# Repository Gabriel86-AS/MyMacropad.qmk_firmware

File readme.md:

PROJECT: A macropad for symbols i use constantly but I often have to copy past them or search for their code to type it in the numerical keyboard.
 (Em Dash)
(Caret)
(Square Root)
(Ohm)
(Plus-Minus)
(Pi)
(Approximately Equal)

To use it should be pretty simple, just solder the components and plug it to the computer (in theory) should work.

I made this project to start learning hardware design

PICTURES

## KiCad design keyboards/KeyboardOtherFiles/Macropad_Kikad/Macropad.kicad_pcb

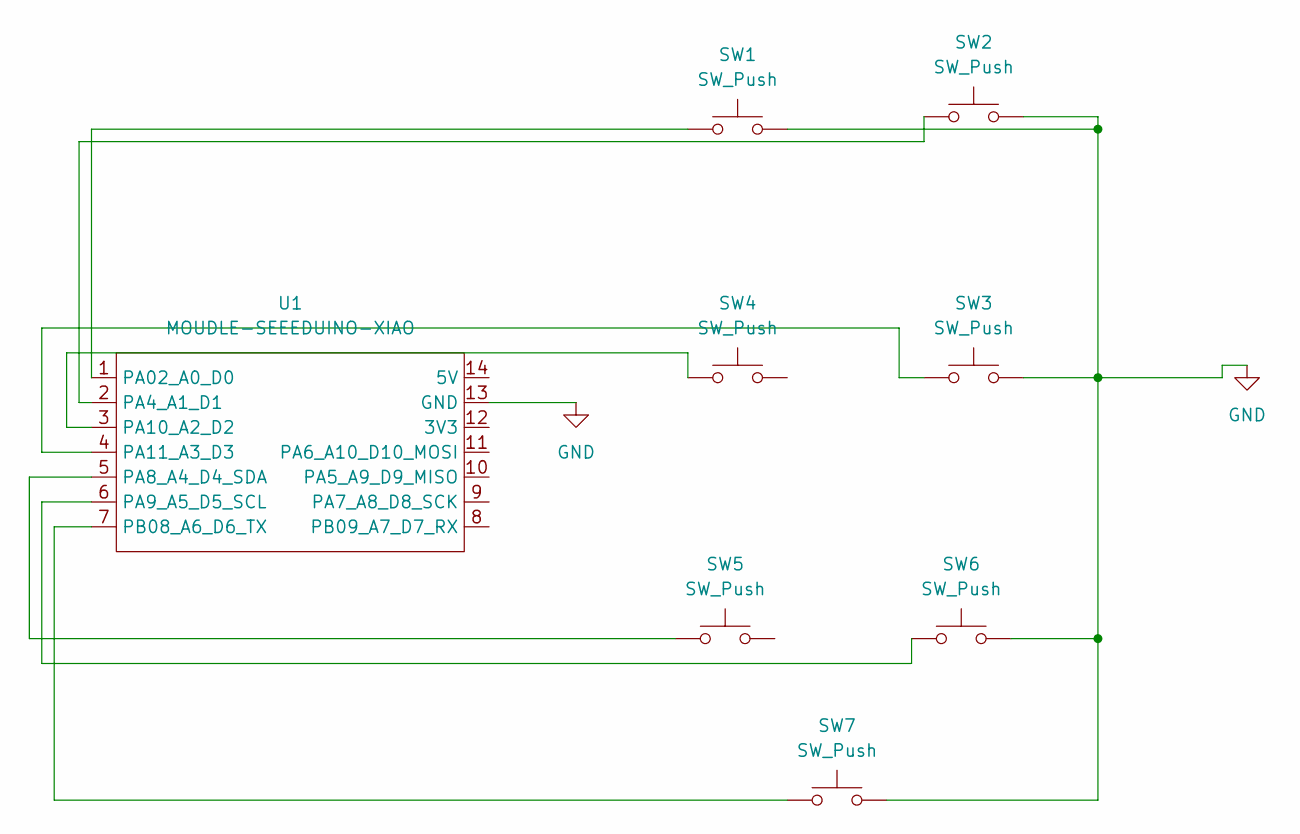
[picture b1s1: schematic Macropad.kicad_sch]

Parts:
SW1, SW2, SW3, SW4, SW5, SW6, SW7: SW_Push; SW_Cherry_MX_1.00u_PCB
U1: MOUDLE-SEEEDUINO-XIAO; XIAO-Generic-Hybrid-14P-2.54-21X17.8MM

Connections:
GND: SW1.2, SW2.2, SW3.2, SW6.2, SW7.2, U1.13 (GND)
unnamed: SW1.1, U1.1 (PA02_A0_D0)
unnamed: SW2.1, U1.2 (PA4_A1_D1)
unnamed: SW5.1, U1.5 (PA8_A4_D4_SDA)
unnamed: SW6.1, U1.6 (PA9_A5_D5_SCL)
unnamed: SW4.1, U1.3 (PA10_A2_D2)
unnamed: SW3.1, U1.4 (PA11_A3_D3)
unnamed: SW7.1, U1.7 (PB08_A6_D6_TX)

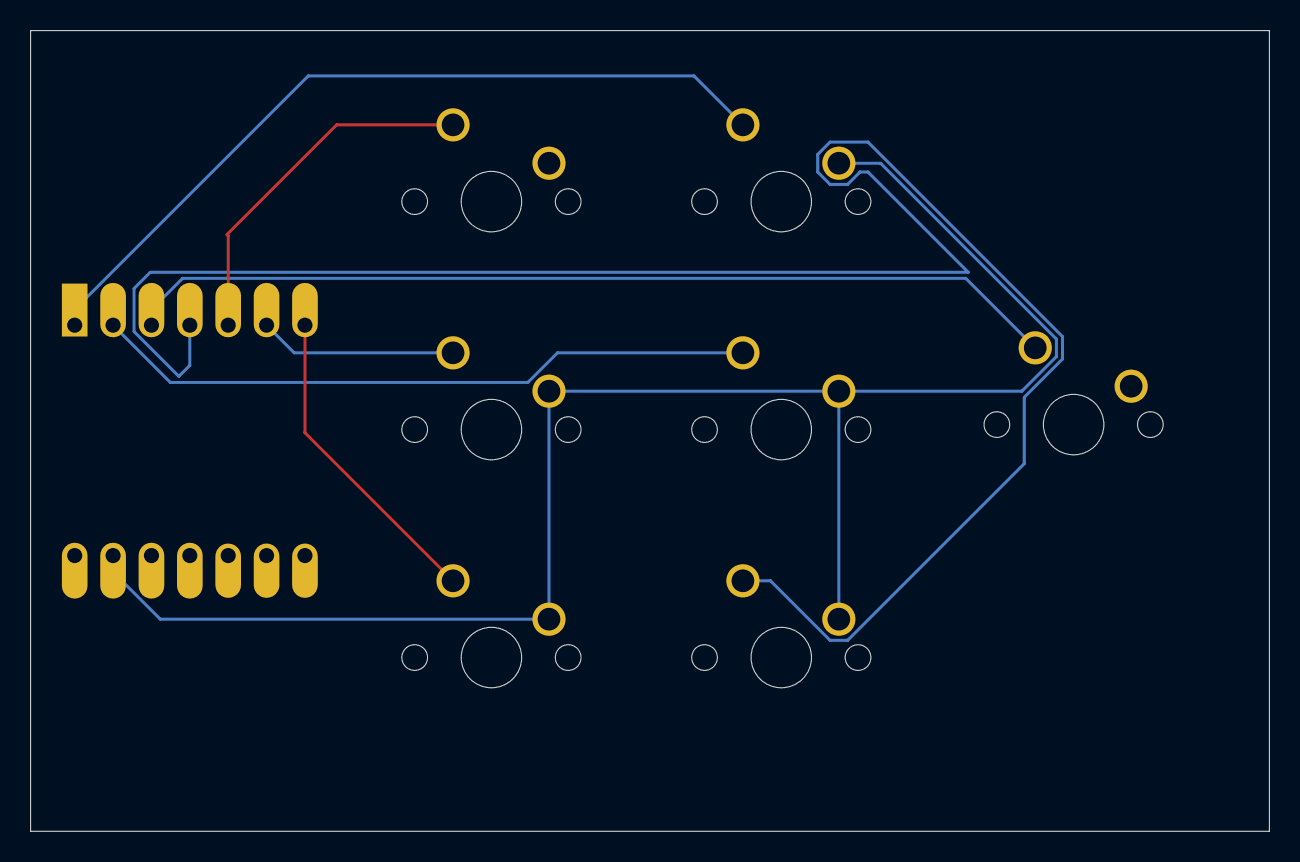
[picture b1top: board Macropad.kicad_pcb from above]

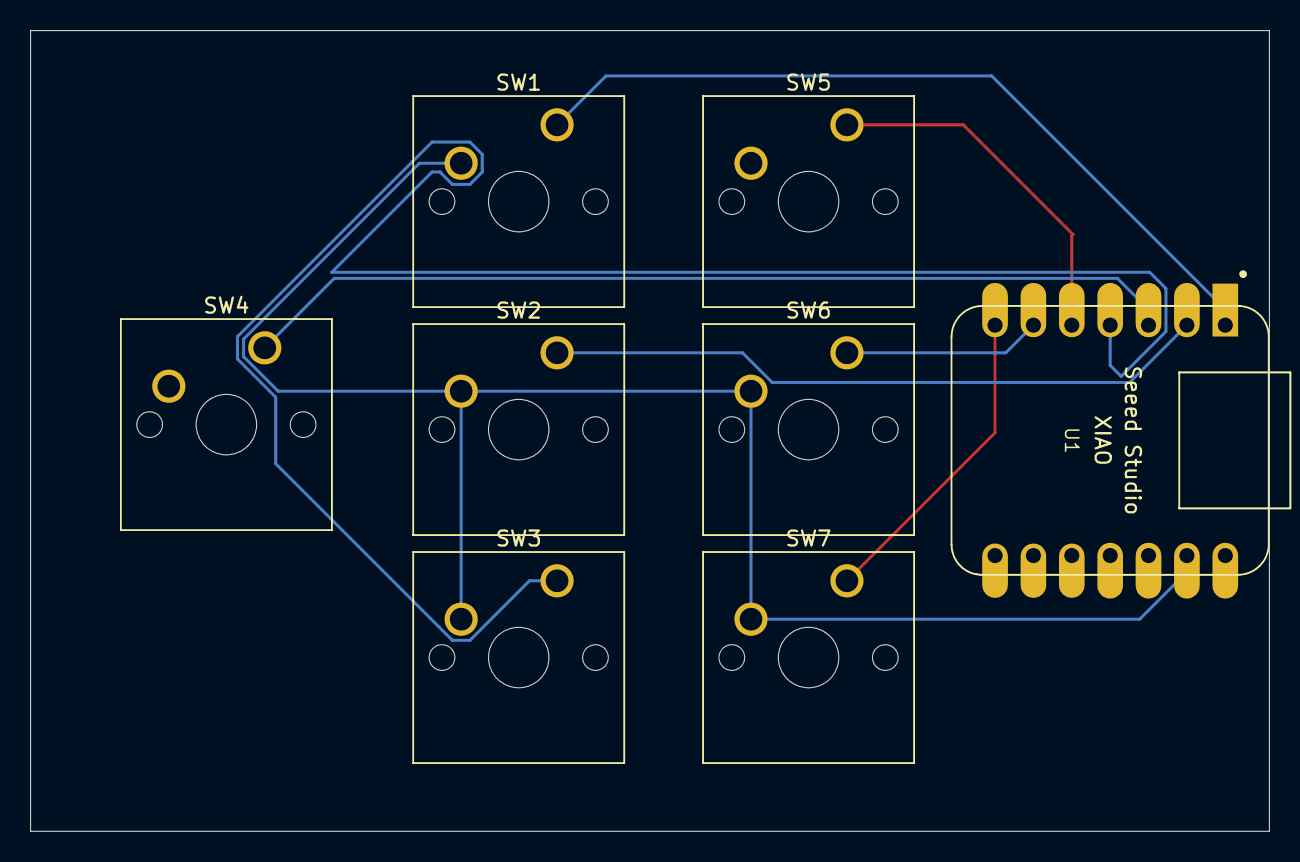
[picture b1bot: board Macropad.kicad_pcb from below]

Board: 2 copper layers, 82.0 x 53.0 mm, 8 parts (8 on the bottom side), 8 nets.

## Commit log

2026-03-05 Add custom 7-key macropad configuration and keymap
2026-03-06 Remove unused keyboard folders
2026-03-06 Add compiled UF2 firmware
2026-03-06 Add auxiliary keyboard files
